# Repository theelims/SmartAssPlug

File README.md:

# SmartAss Plug - A Smart Butt Plug

Everything becomes "smart" these days. And there is no exception for butt plugs. While many butt plugs claim "smartness", just connecting it to the internet typically only means a remote control with more range. However **SmartAss Plug** has some more tricks up its sleeves. It's main purpose is not to vibrate a butt, but to sense and gauge sexual arousal. Having a reliable way to measure sexual arousal and orgasms opens up many possibility for the kinky minded person. Pneumatic anal probes have long time being the preferred choice in the clinical sector. However, in the kinky maker space the inflatable butt plug has gained more traction. Not least because of open source projects like the [nogasm](https://github.com/nogasm/nogasm) and the [protogasm](https://github.com/night-howler/protogasm). However, the inflatable butt plug suffers from a really bad signal to noise ratio. **SmartAss Plug** tries to build on these groundwork adding a more reliable sensor element, a more robust clench detection algorithm utilizing a kalman filter and calculus. All in a self-contained unit doing away any trip wires. In order to control a pleasure inducing device it connects to [XToys](https://xtoys.app/) or [buttplug.io](https://buttplug.io/) / [infitface](https://github.com/intiface/intiface-central).

Naturally it vibrates, too (kind of a the minimum requirement, obviously) and comes with more fun like a 9-DoF IMU and RGB Leds. Because, why not?

And last but not least, you are finally able to serve a website straight from your ass. How far has humanity come?

## Features

- Measures the involuntarily clenches of the pelvic floor to derive the arousal level of the wearer.
- Arousal classifier with the states "neutral", "aroused", "edging" or "orgasm".
- Vibration motor (plug sizes S & M only) for feedback, cheating in chess or stimulation.
- 9-DoF IMU to determine the absolute position of the plug for position training. (Not implemented, yet)
- Connects to your Wi-Fi or creates its own access point.
- Internal webserver to serve you the user interface straight from your butt.
- The inevitable RGB-led to make your butt shine colorful.
- Open WebSocket based API to integrate with your projects. (XToys and Buttplug.io support are pending)

## F.A.Q.

### What is the benefit of the coiled tube over an inflatable butt plug?

Using an inflatable butt plug is the traditional approach for edging and orgasm detection as introduced by the original nogasm. However, using this comes with some notable downsides. For some the size of these plugs can be daunting. Also the inflated portion - which is the actual sensor - sits behind the anal sphincter most of the time. As the signal we are looking for is the involuntarily clenching of the pelvic floor, the signal to noise ratio of an inflatable butt plug is not that great. It does pick up a lot of noise like breathing or even the heart beat. These signals can falsely trigger the algorithm leading to unsatisfying results. The coiled silicone tube sits exactly where the clenches happen resulting in a much cleaner signal to start with.

### Where can I buy this?

So far you can't buy it. You need to build it yourself sourcing all the required materials on your own. Consult the [sourcing guide](https://theelims.github.io/SmartAssPlug/sourcing/) for more information.

### Does it integrate with XToys or Buttplug.io?

SmartAss Plug offers a WebSocket API which makes it easy to integrate. XToys and Buttplug.io support is planned, but not implemented, yet.

### Is it available in different sizes?

Yes, the plug is available in 3 different sizes to accommodate a wide range of tastes.

|  Size  | Vibration | Diameter |
| :----: | :-------: | :------: |
| **XS** |    No     |  25 mm   |
| **S**  |    Yes    |  30 mm   |
| **M**  |    Yes    |  38 mm   |

## Contributors and Sources of Inspiration

- **Rudolf**, who came up with the [coiled silicone tube](https://www.thingiverse.com/thing:3543727) as sensor element and even has written a [scientific paper](https://www.degruyter.com/document/doi/10.1515/pjbr-2020-0014/pdf) on that topic.
- **Rhobot** with the original [nogasm project](https://github.com/nogasm/nogasm)
- **Onwrikbaar** with his bullfrog, who refined the simple [nogasm algorithm](https://github.com/Onwrikbaar/Bullfrog) with a peak summation and decay function.
- **night-howler** who contributed a breadboard friendly version of the nogasm called [protogasm](https://github.com/night-howler/protogasm).
- **Maus-Tec** who manufactures and sells the [Edge-O-Matic](https://github.com/MausTec/edge-o-matic-3000)
- **Skier23** who curates a [repository](https://github.com/Edging-Machines/Edging-Machines) and [discord](https://discord.gg/EvYbZBf) with all information regarding the topic.
- **Alex-R&D**

## License

Copyright &copy; 2023 by <a href="https://github.com/theelims"  target="_blank" rel="noopener">elims</a>

All work - software and hardware - is licensed under the

Creative Commons Attribution-ShareAlike 4.0 International Public License\*\*

For a full text of the license visit [CC-BY-SA 4.0](https://creativecommons.org/licenses/by-sa/4.0/).

# For further information visit the [project site](https://theelims.github.io/SmartAssPlug/).

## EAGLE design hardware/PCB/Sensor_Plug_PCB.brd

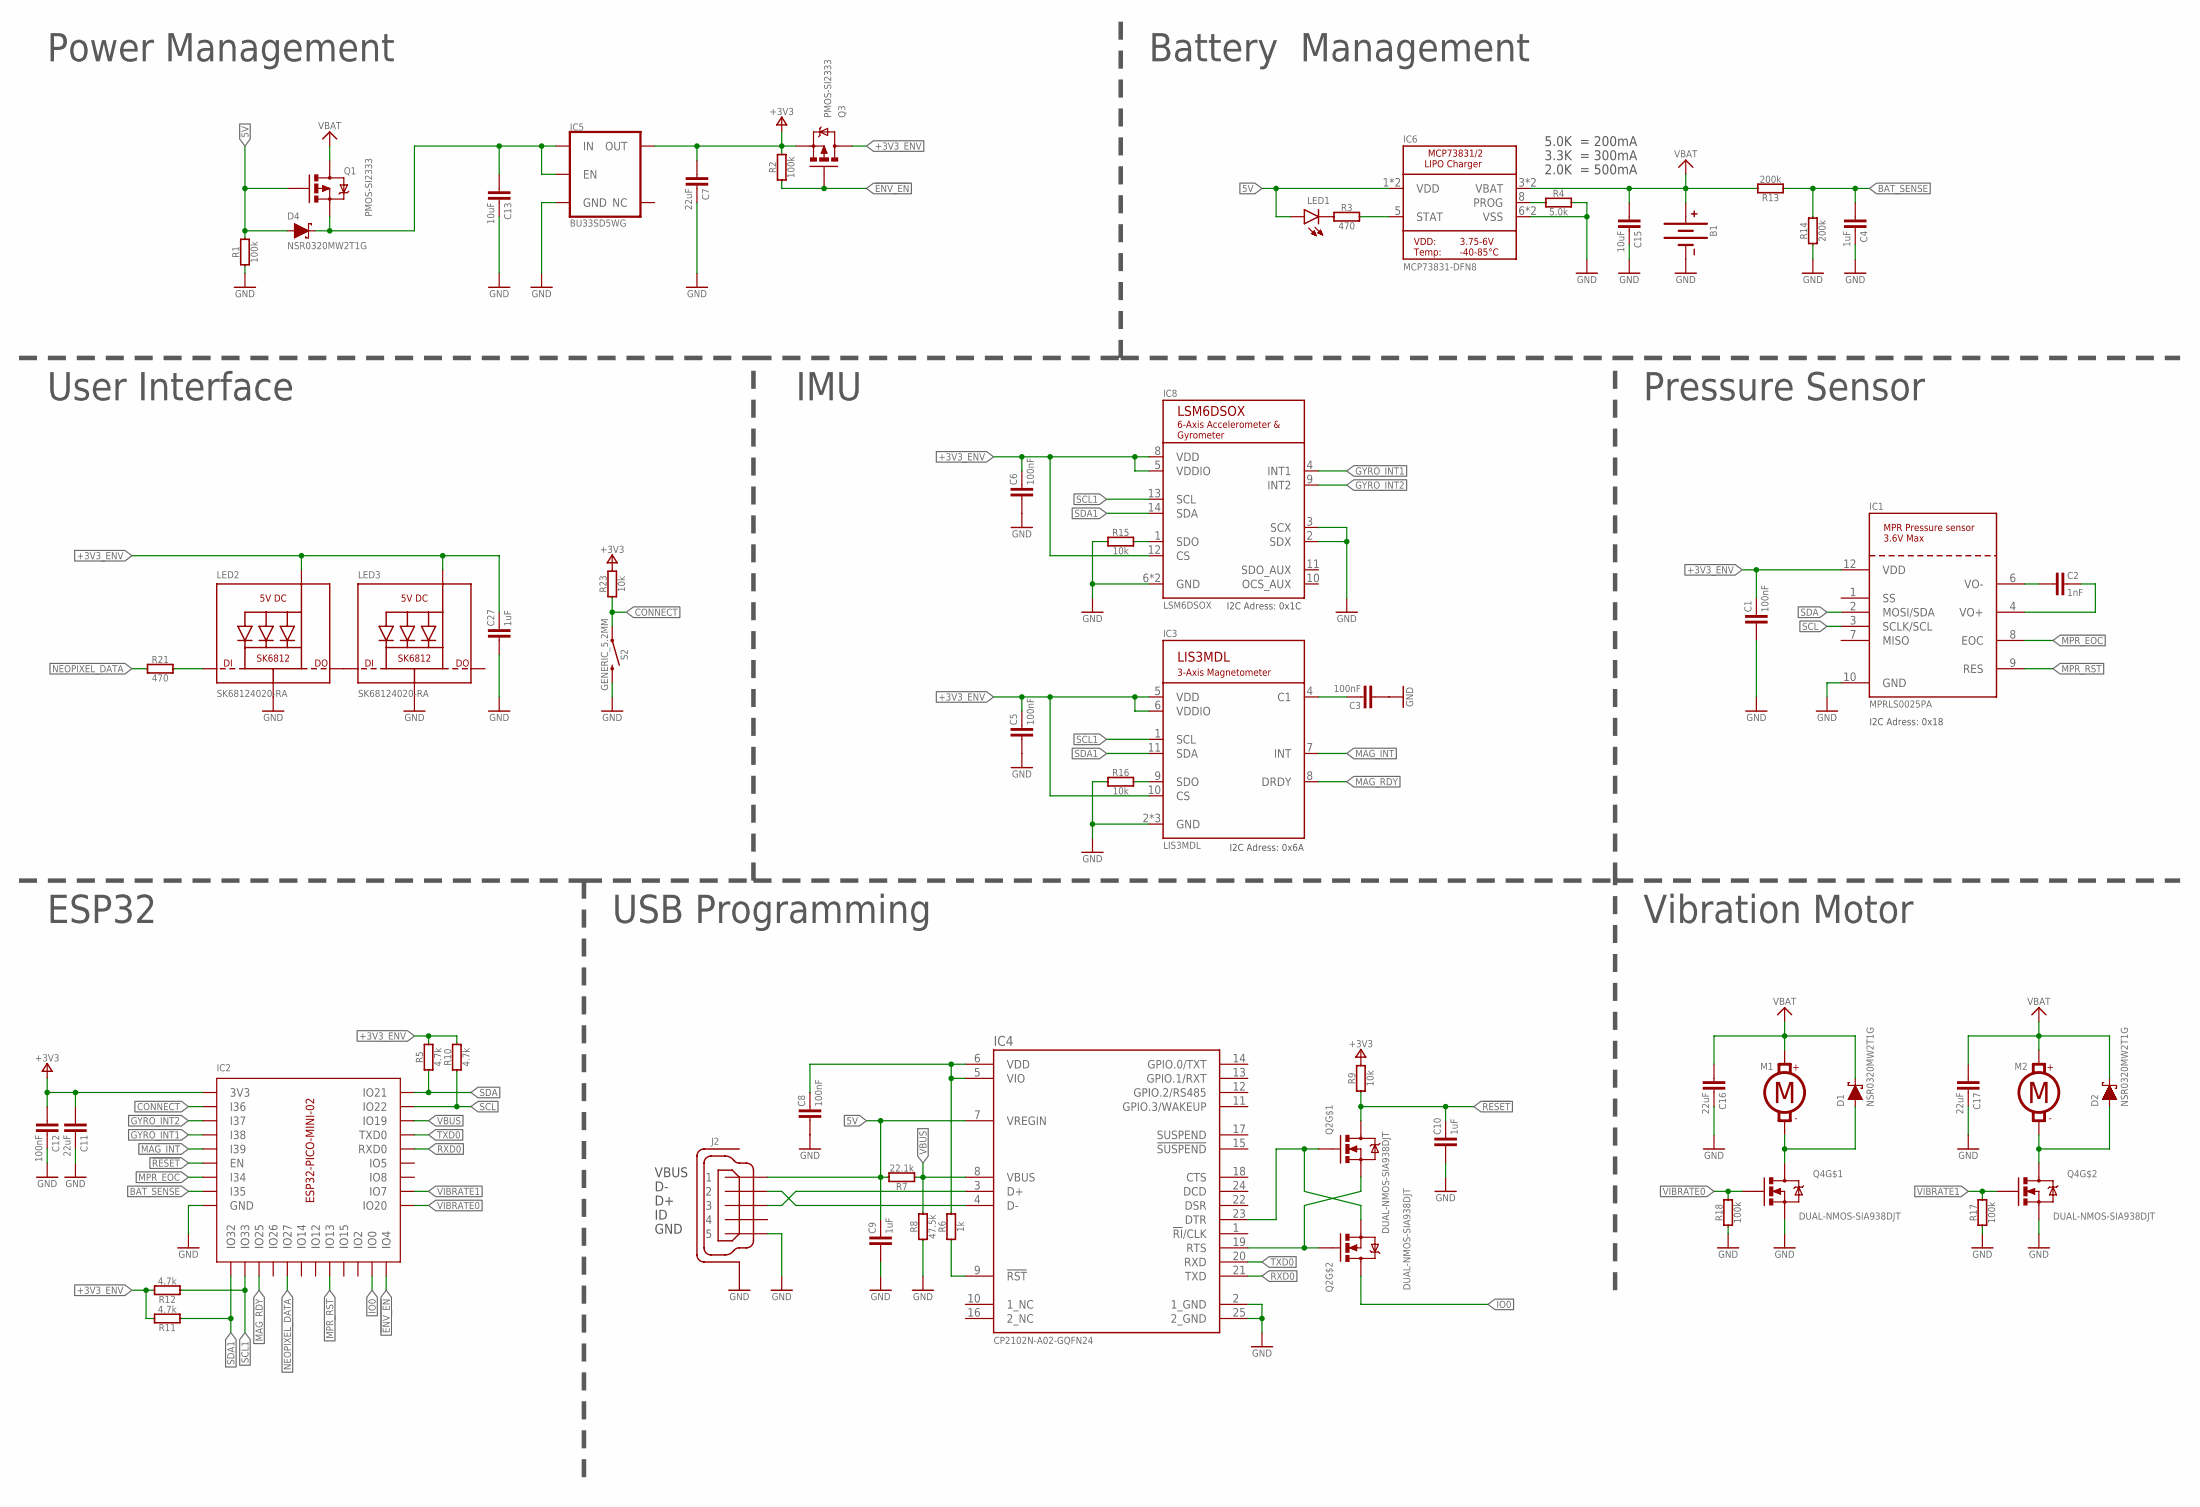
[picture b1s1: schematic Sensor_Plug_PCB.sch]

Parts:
B1: LIPO-JST_PH_SMDV-02; JST_PH_SMDV-02
C1, C3, C5, C6, C8, C12: 100nF; C0603
C2: 1nF; C0603
C4, C9, C10, C27: 1uF; C0603
C7, C11, C16, C17: 22uF; C0805
C13, C15: 10uF; C0805
D1, D2, D4: NSR0320MW2T1G; SOD-323
IC1: MPRLS0025PA
IC2: EPS32-PICO-MINI-02; ESP32-PICO-MINI-02
IC3: LIS3MDL; LGA12_2X2MM
IC4: CP2102N-A02-GQFN24; QFN24
IC5: BU33SD5WG; SOT23-5
IC6: MCP73831-DFN8; DFN8_2X3
IC8: LSM6DSOX; LGA-14L
J2: -; ZX62-AB-5PA
LED1: LED-0603-SIDEVIEW; LED_0603_SIDEVIEW
LED2, LED3: SK68124020-RA; SK6812-4020-SIDE
M1, M2: MOTOR-PADS
Q1, Q3: PMOS-SI2333; SOT23-3
Q2, Q4: DUAL-NMOS-SIA938DJT; POWERPAK_SC70-6L_DUAL
R1, R2, R17, R18: 100k; R0603
R3, R21: 470; R0603
R4: 5.0k; R0603
R5, R10, R11, R12: 4.7k; R0603
R6: 1k; R0603
R7: 22.1k; R0603
R8: 47.5k; R0603
R9, R15, R16, R23: 10k; R0603
R13, R14: 200k; R0603
S2: GENERIC_5.2MM; C&K_KMS

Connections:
5V: C9.1, D4.A, IC4.7 (VREGIN), IC6.1 (VDD), IC6.2 (VDD), J2.1, LED1.A, Q1.1 (G), R1.2, R7.2
!ENV_EN: IC2.P$24 (IO4), Q3.1 (G), R2.1
!RESET: C10.1, IC2.P$8 (EN), Q2.6 (D), Q2.7 (D), R9.1
+3V3: C7.2, C11.2, C12.2, IC2.P$3 (3V3), IC5.5 (OUT), Q3.2 (S), R2.2, R9.2, R23.2
+3V3_ENV: C1.1, C5.1, C6.1, C27.1, IC1.12 (VDD), IC3.5 (VDD), IC3.6 (VDDIO), IC3.10 (CS), IC8.5 (VDDIO), IC8.8 (VDD), IC8.12 (CS), LED2.VDD, LED3.VDD, Q3.3 (D), R5.2, R10.2, R11.2, R12.2
BAT_SENSE: C4.2, IC2.P$10 (I35), R13.1, R14.2
CHARGING: IC6.5 (STAT), R3.2
CONNECT: IC2.P$4 (I36), R23.1, S2.1, S2.5 (1)
DTR: IC4.23 (DTR), Q2.2 (G), Q2.4 (S)
GND: B1.1 (-), C1.2, C3.2, C4.1, C5.2, C6.2, C7.1, C8.2, C9.2, C10.2, C11.1, C12.1, C13.1, C15.1, C16.1, C17.1, C27.2, IC1.10 (GND), IC2.P$1 (GND), IC2.P$2 (GND), IC2.P$11 (GND), IC2.P$14 (GND), IC2.P$36 (GND), IC2.P$37 (GND), IC2.P$38 (GND), IC2.P$39 (GND), IC2.P$40 (GND), IC2.P$41 (GND), IC2.P$42 (GND), IC2.P$43 (GND), IC2.P$44 (GND), IC2.P$45 (GND), IC2.P$46 (GND), IC2.P$47 (GND), IC2.P$48 (GND), IC2.P$49 (GND), IC2.P$50 (GND), IC2.P$51 (GND), IC2.P$52 (GND), IC2.P$53 (GND), IC2.P$54 (GND), IC2.P$55 (GND), IC2.P$56 (GND), IC2.P$57 (GND), IC2.P$58 (GND), IC2.P$59 (GND), IC2.P$60 (GND), IC2.P$61 (GND), IC3.2 (GND), IC3.3 (GND), IC3.12 (GND), IC4.2 (1_GND), IC4.25 (2_GND), IC5.2 (GND), IC6.6 (VSS), IC6.9 (VSS), IC8.2 (SDX), IC8.3 (SCX), IC8.6 (GND), IC8.7 (GND), J2.5, J2.6 (SH), J2.7 (SH), J2.8 (SH), J2.9 (SH), J2.10 (SH), J2.11 (SH), LED2.GND, LED3.GND, Q4.1 (S), Q4.4 (S), R1.1, R4.2, R8.1, R14.1, R15.1, R16.1, R17.1, R18.1, S2.2, S2.3 (2), S2.4 (2)
GYRO_INT1: IC2.P$6 (I38), IC8.4 (INT1)
GYRO_INT2: IC2.P$5 (I37), IC8.9 (INT2)
IO0: IC2.P$23 (IO0), Q2.3 (D), Q2.8 (D)
MAG_INT: IC2.P$7 (I39), IC3.7 (INT)
MAG_RDY: IC2.P$15 (IO25), IC3.8 (DRDY)
MPR_EOC: IC1.8 (EOC), IC2.P$9 (I34)
MPR_RST: IC1.9 (RES), IC2.P$20 (IO13)
unnamed: C8.1, IC4.5 (VIO), IC4.6 (VDD), R6.2
unnamed: C13.2, D4.C, IC5.1 (IN), IC5.3 (EN), Q1.2 (S)
unnamed: C2.2, IC1.6 (VO-)
unnamed: C2.1, IC1.4 (VO+)
unnamed: C3.1, IC3.4 (C1)
unnamed: IC4.4 (D-), J2.2
unnamed: IC4.3 (D+), J2.3
unnamed: LED1.C, R3.1
unnamed: D1.A, M1.N, Q4.6 (D), Q4.7 (D)
unnamed: IC4.9 (!RST!), R6.1
unnamed: IC6.8 (PROG), R4.1
unnamed: LED2.DOUT (DO), LED3.DIN (DI)
unnamed: D2.A, M2.N, Q4.3 (D), Q4.8 (D)
unnamed: IC8.1 (SDO), R15.2
unnamed: IC3.9 (SDO), R16.2
unnamed: LED2.DIN (DI), R21.1
NEOPIXEL_DATA: IC2.P$17 (IO27), R21.2
RTS: IC4.19 (RTS), Q2.1 (S), Q2.5 (G)
RXD0: IC2.P$30 (RXD0), IC4.21 (TXD)
SCL: IC1.3 (SCLK/SCL), IC2.P$34 (IO22), R10.1
SCL1: IC2.P$13 (IO33), IC3.1 (SCL), IC8.13 (SCL), R12.1
SDA: IC1.2 (MOSI/SDA), IC2.P$35 (IO21), R5.1
SDA1: IC2.P$12 (IO32), IC3.11 (SDA), IC8.14 (SDA), R11.1
TXD0: IC2.P$31 (TXD0), IC4.20 (RXD)
VBAT: B1.2 (+), C15.2, C16.2, C17.2, D1.C, D2.C, IC6.3 (VBAT), IC6.4 (VBAT), M1.P, M2.P, Q1.3 (D), R13.2
VBUS: IC2.P$33 (IO19), IC4.8 (VBUS), R7.1, R8.2
VIBRATE0: IC2.P$26 (IO20), Q4.2 (G), R18.2
VIBRATE1: IC2.P$27 (IO7), Q4.5 (G), R17.2

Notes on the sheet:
Power Management
Battery Management
ESP32
USB Programming
Pressure Sensor
User Interface
IMU
3.3K = 300mA
2.0K = 500mA
I2C Adress: 0x18
Vibration Motor
I2C Adress: 0x6A
I2C Adress: 0x1C
5.0K = 200mA

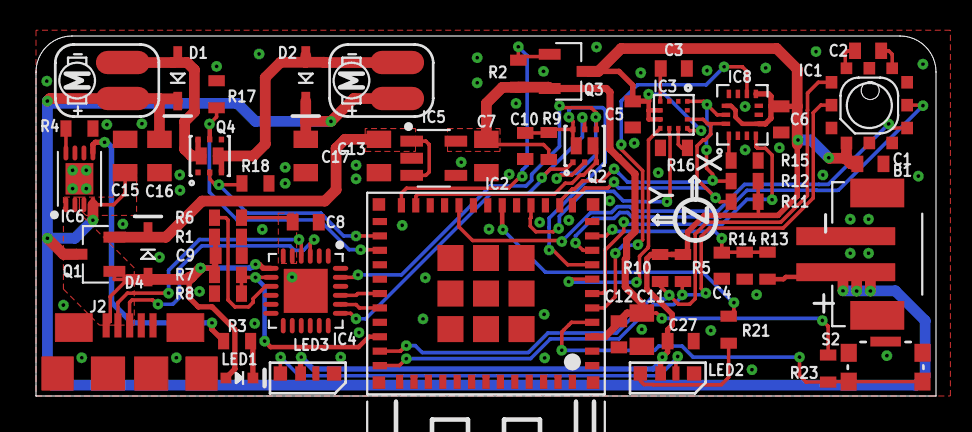
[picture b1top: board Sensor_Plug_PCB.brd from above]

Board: 2 copper layers, 50.0 x 20.0 mm, 59 parts (0 on the bottom side), 45 nets.

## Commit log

2022-09-18 Create LICENCE
2023-02-04 Added hardware
2023-02-04 CSV Syntax
2023-02-04 More Syntax CSV
2023-02-05 new PCB export
2023-02-05 Update Docs
2023-02-06 Updated docs
2023-02-07 added step files
2023-02-08 restructured docs
2023-02-08 CI compiles different then local dev
2023-02-08 finished assembly docs
2023-02-09 Updated docs once again
2023-02-10 Some spelling
2023-02-18 fixed broken links to sourcing guide
2023-03-17 Change R5 to reduce charge current
    Charge current was too ambitious leading to excessive heating during charging. This fixes the heat issue.
2023-03-17 Deployed eeca3fc with MkDocs version: 1.4.2
2023-08-04 ESP32-sveltekit base
2023-08-10 data streaming
2023-08-23 CBOR data streaming
2023-09-02 hard fork ESPAsyncWebServer
2023-09-04 hard fork libCBOR into the repo and datalogging
2023-09-04 Added internal vibrator
2023-09-05 Modularization of the codebase
2023-09-06 added service with config. Kalman Filter
2023-09-06 Showcase linker failure IRAM
2023-09-06 added a glitch filter
2023-09-06 Filter UI
2023-09-06 Adjusted axis realtime data
2023-09-06 Update build flag
2023-09-07 costume partitions.csv
2023-09-07 Further tests
2023-09-07 platformio
2023-09-07 Issues with latest platformio espressif32
2023-09-12 Fix boot loop issue
2023-09-22 added System Metrics
2024-02-07 new PCB revision
